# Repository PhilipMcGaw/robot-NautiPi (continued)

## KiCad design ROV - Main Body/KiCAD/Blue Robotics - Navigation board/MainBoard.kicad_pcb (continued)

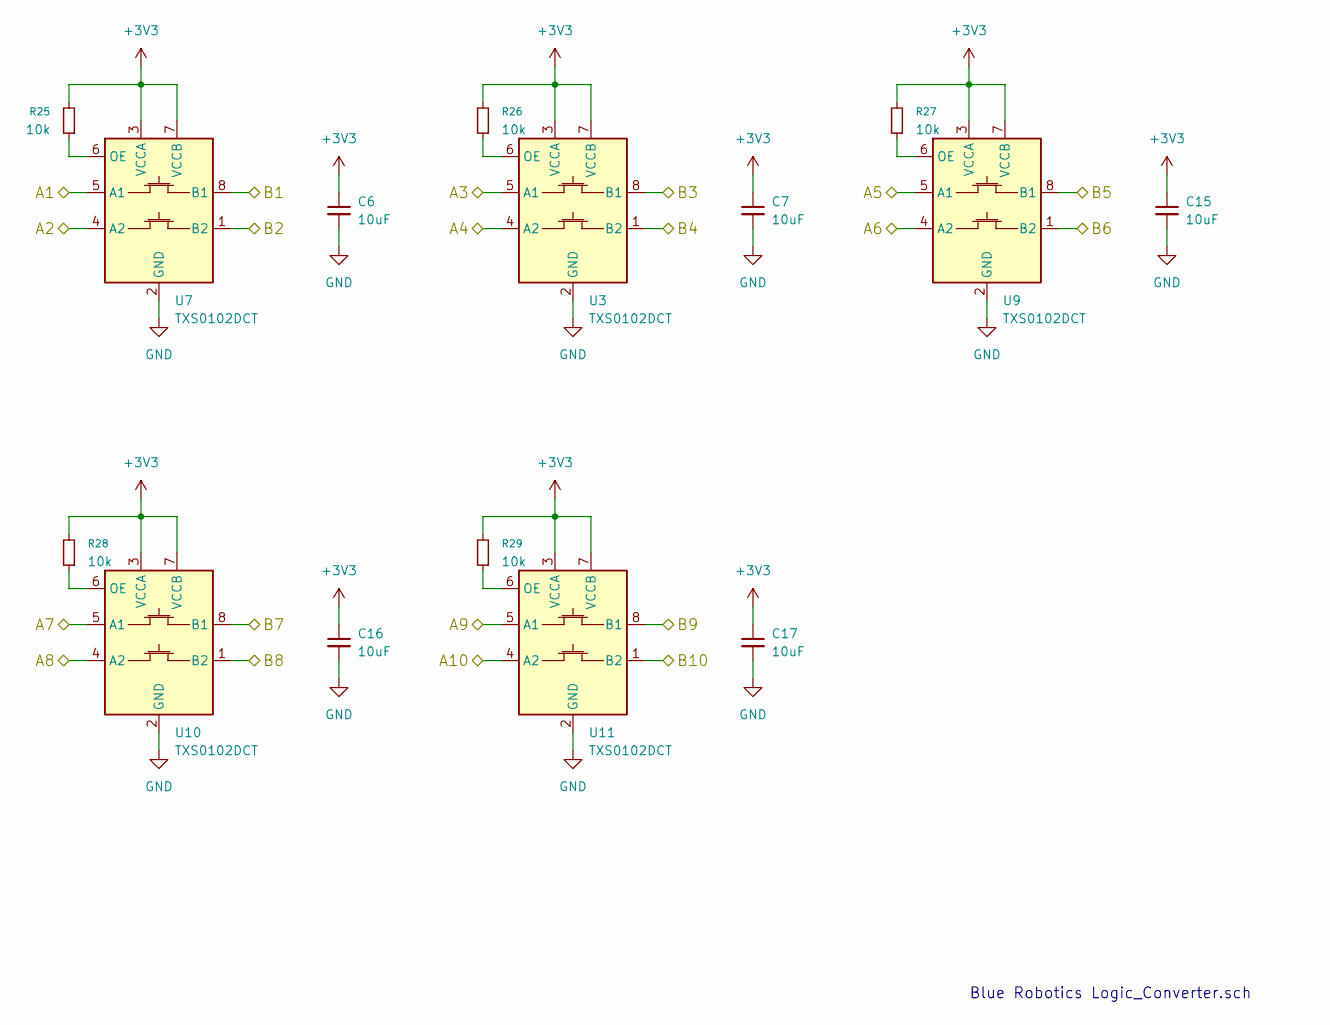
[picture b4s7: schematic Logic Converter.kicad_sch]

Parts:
C6, C7, C15, C16, C17: 10uF; C_0805_2012Metric_Pad1.18x1.45mm_HandSolder
R25, R26, R27, R28, R29: 10k; R_0805_2012Metric_Pad1.20x1.40mm_HandSolder
U3, U7, U9, U10, U11: TXS0102DCT; SSOP-8_2.95x2.8mm_P0.65mm; Farnell 3120980

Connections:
+3V3: C6.1, C7.1, C15.1, C16.1, C17.1, R25.2, R26.2, R27.2, R28.2, R29.2, U3.3 (VCCA), U3.7 (VCCB), U7.3 (VCCA), U7.7 (VCCB), U9.3 (VCCA), U9.7 (VCCB), U10.3 (VCCA), U10.7 (VCCB), U11.3 (VCCA), U11.7 (VCCB); also elsewhere on the board
/RX1: U7.8 (B1); also elsewhere on the board
/RX1_RPI: U7.5 (A1); also elsewhere on the board
/RX3: U3.8 (B1); also elsewhere on the board
/RX3_RPI: U3.5 (A1); also elsewhere on the board
/RX4: U9.1 (B2); also elsewhere on the board
/RX4_RPI: U9.4 (A2); also elsewhere on the board
/RX5: U10.8 (B1); also elsewhere on the board
/RX5_RPI: U10.5 (A1); also elsewhere on the board
/SCL6: U11.8 (B1); also elsewhere on the board
/SCL6_RPI: U11.5 (A1); also elsewhere on the board
/SDA6: U11.1 (B2); also elsewhere on the board
/SDA6_RPI: U11.4 (A2); also elsewhere on the board
/TX1: U7.1 (B2); also elsewhere on the board
/TX1_RPI: U7.4 (A2); also elsewhere on the board
/TX3: U3.1 (B2); also elsewhere on the board
/TX3_RPI: U3.4 (A2); also elsewhere on the board
/TX4: U9.8 (B1); also elsewhere on the board
/TX4_RPI: U9.5 (A1); also elsewhere on the board
/TX5: U10.1 (B2); also elsewhere on the board
/TX5_RPI: U10.4 (A2); also elsewhere on the board
GND: C6.2, C7.2, C15.2, C16.2, C17.2, U3.2 (GND), U7.2 (GND), U9.2 (GND), U10.2 (GND), U11.2 (GND); also elsewhere on the board
unnamed: R26.1, U3.6 (OE)
unnamed: R25.1, U7.6 (OE)
unnamed: R27.1, U9.6 (OE)
unnamed: R28.1, U10.6 (OE)
unnamed: R29.1, U11.6 (OE)

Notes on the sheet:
Blue Robotics Logic_Converter.sch

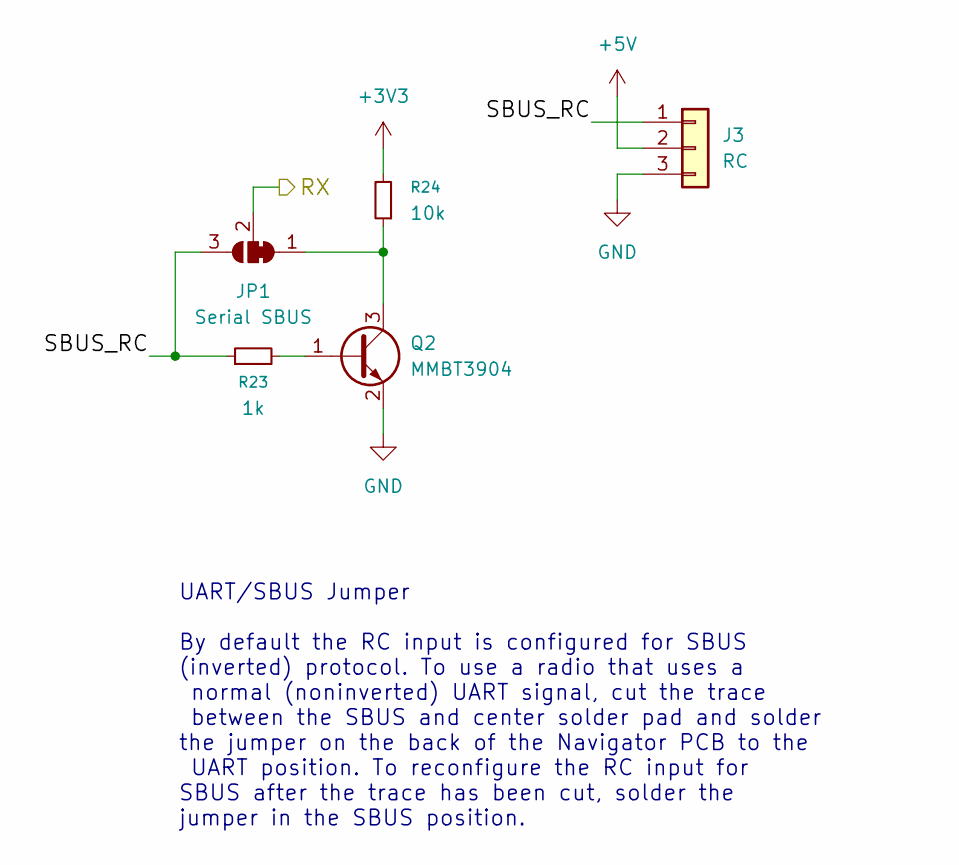
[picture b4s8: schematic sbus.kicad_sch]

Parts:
J3: RC; PinHeader_1x03_P2.54mm_Vertical
JP1: Serial SBUS; SolderJumper-3_P1.3mm_Bridged12_RoundedPad1.0x1.5mm
Q2: MMBT3904; SOT-23
R23: 1k; R_0805_2012Metric_Pad1.20x1.40mm_HandSolder
R24: 10k; R_0805_2012Metric_Pad1.20x1.40mm_HandSolder

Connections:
+3V3: R24.2; also elsewhere on the board
+5V: J3.2; also elsewhere on the board
/RX1: JP1.2 (C); also elsewhere on the board
/SBUS/SBUS_RC: J3.1, JP1.3 (B), R23.1
GND: J3.3, Q2.2 (E); also elsewhere on the board
unnamed: JP1.1 (A), Q2.3 (C), R24.1
unnamed: Q2.1 (B), R23.2

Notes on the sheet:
UART/SBUS Jumper By default the RC input is configured for SBUS (inverted) protocol. To use a radio that uses a normal (noninverted) UART signal, cut the trace between the SBUS and center solder pad and solder the jumper on the back of the Navigator PCB to the UART position. To reconfigure the RC i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

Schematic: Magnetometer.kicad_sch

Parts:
C27: 10uF; C_0805_2012Metric_Pad1.18x1.45mm_HandSolder
C28: 1uF; C_0805_2012Metric_Pad1.18x1.45mm_HandSolder
C29, C30: 100nF; C_0805_2012Metric_Pad1.18x1.45mm_HandSolder

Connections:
+3V3: C27.1, C28.1, C29.1, C30.1; also elsewhere on the board
GND: C27.2, C28.2, C29.2, C30.2; also elsewhere on the board

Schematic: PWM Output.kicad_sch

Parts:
J2: PWM 1-4; JST_GH_BM05B-GHS-TBT_1x05-1MP_P1.25mm_Vertical
J4: PWM 5-8; JST_GH_BM05B-GHS-TBT_1x05-1MP_P1.25mm_Vertical
J11: Servo04; PinHeader_1x03_P2.54mm_Vertical
J12: Servo01; PinHeader_1x03_P2.54mm_Vertical
J13: Servo05; PinHeader_1x03_P2.54mm_Vertical
J14: Servo06; PinHeader_1x03_P2.54mm_Vertical
J15: Servo07; PinHeader_1x03_P2.54mm_Vertical
J16: Servo08; PinHeader_1x03_P2.54mm_Vertical
J21: Servo09; PinHeader_1x03_P2.54mm_Vertical
J25: Servo10; PinHeader_1x03_P2.54mm_Vertical
J26: Servo11; PinHeader_1x03_P2.54mm_Vertical
J27: Servo12; PinHeader_1x03_P2.54mm_Vertical
J28: Servo13; PinHeader_1x03_P2.54mm_Vertical
J29: Servo14; PinHeader_1x03_P2.54mm_Vertical
J30: Servo15; PinHeader_1x03_P2.54mm_Vertical
J31: Servo16; PinHeader_1x03_P2.54mm_Vertical
J32: Servo02; PinHeader_1x03_P2.54mm_Vertical
J41: Servo03; PinHeader_1x03_P2.54mm_Vertical
R44: 10k; R_0805_2012Metric_Pad1.20x1.40mm_HandSolder
RN1, RN2, RN3, RN4: 220; R_Array_Convex_4x1206
U1: PCA9685PW; TSSOP-28_4.4x9.7mm_P0.65mm

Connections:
+3V3: R44.1, U1.28 (VDD); also elsewhere on the board
/PWM Output/PWM01: J2.1, J12.1, RN1.8 (R1.2)
/PWM Output/PWM02: J2.2, J32.1, RN1.7 (R2.2)
/PWM Output/PWM03: J2.3, J41.1, RN1.6 (R3.2)
/PWM Output/PWM04: J2.4, J11.1, RN1.5 (R4.2)
/PWM Output/PWM05: J4.1, J13.1, RN2.8 (R1.2)
/PWM Output/PWM06: J4.2, J14.1, RN2.7 (R2.2)
/PWM Output/PWM07: J4.3, J15.1, RN2.6 (R3.2)
/PWM Output/PWM08: J4.4, J16.1, RN2.5 (R4.2)
/PWM Output/PWM09: J21.1, RN3.8 (R1.2)
/PWM Output/PWM10: J25.1, RN3.7 (R2.2)
/PWM Output/PWM11: J26.1, RN3.6 (R3.2)
/PWM Output/PWM12: J27.1, RN3.5 (R4.2)
/PWM Output/PWM13: J28.1, RN4.8 (R1.2)
/PWM Output/PWM14: J29.1, RN4.7 (R2.2)
/PWM Output/PWM15: J30.1, RN4.6 (R3.2)
/PWM Output/PWM16: J31.1, RN4.5 (R4.2)
/PWM_OE: R44.2, U1.23 (~OE); also elsewhere on the board
/SCL4: U1.26 (SCL); also elsewhere on the board
/SDA4: U1.27 (SDA); also elsewhere on the board
GND: J2.5, J4.5, J11.3, J12.3, J13.3, J14.3, J15.3, J16.3, J21.3, J25.3, J26.3, J27.3, J28.3, J29.3, J30.3, J31.3, J32.3, J41.3, U1.1 (A0), U1.2 (A1), U1.3 (A2), U1.4 (A3), U1.5 (A4), U1.14 (VSS), U1.24 (A5), U1.25 (EXTCLK); also elsewhere on the board
unnamed: RN1.1 (R1.1), U1.6 (LED0)
unnamed: RN1.2 (R2.1), U1.7 (LED1)
unnamed: RN1.3 (R3.1), U1.8 (LED2)
unnamed: RN1.4 (R4.1), U1.9 (LED3)
unnamed: RN2.1 (R1.1), U1.10 (LED4)
unnamed: RN2.2 (R2.1), U1.11 (LED5)
unnamed: RN2.3 (R3.1), U1.12 (LED6)
unnamed: RN2.4 (R4.1), U1.13 (LED7)
unnamed: RN3.1 (R1.1), U1.15 (LED8)
unnamed: RN3.2 (R2.1), U1.16 (LED9)
unnamed: RN3.3 (R3.1), U1.17 (LED10)
unnamed: RN3.4 (R4.1), U1.18 (LED11)
unnamed: RN4.1 (R1.1), U1.19 (LED12)
unnamed: RN4.2 (R2.1), U1.20 (LED13)
unnamed: RN4.3 (R3.1), U1.21 (LED14)
unnamed: RN4.4 (R4.1), U1.22 (LED15)
SERVO_BEC: J11.2, J12.2, J13.2, J14.2, J15.2, J16.2, J21.2, J25.2, J26.2, J27.2, J28.2, J29.2, J30.2, J31.2, J32.2, J41.2; also elsewhere on the board

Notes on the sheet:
This is dervied from the Blue Robotics pwm-output.sch Local X1 has been ommited, and external clock taken to ground. Servo connectors have been broken out onto 1x03 connectors
Mating JST GH Plug and Crimp Pins GHR-05V-S (housing) SSHL-002T-P0.2 (pin)

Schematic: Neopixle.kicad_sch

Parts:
C20: 100nF; C_0805_2012Metric_Pad1.18x1.45mm_HandSolder
D20: WS2812B; LED_WS2812B_PLCC4_5.0x5.0mm_P3.2mm

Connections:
+5V: C20.1, D20.1 (VDD); also elsewhere on the board
/RGB_LED: D20.4 (DIN); also elsewhere on the board
GND: C20.2, D20.3 (VSS); also elsewhere on the board

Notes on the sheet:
This is dervied from the Blue Robotics neopixel.sch Local U13 has been ommited, and neopixle has been changed from SK6812 to a WS2812B.

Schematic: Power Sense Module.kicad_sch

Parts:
C18: 0.1uF; C_0805_2012Metric_Pad1.18x1.45mm_HandSolder
C19: 1uF; C_0805_2012Metric_Pad1.18x1.45mm_HandSolder
R3: 4.7k; R_0805_2012Metric_Pad1.20x1.40mm_HandSolder
R12: 47.5k; R_0805_2012Metric_Pad1.20x1.40mm_HandSolder
R13: 4.75k; R_0805_2012Metric_Pad1.20x1.40mm_HandSolder
U6: ACS781xLRTR-100U; Allegro_PSOF-7_4.8x6.4mm_P1.60mm

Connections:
+3V3: C18.1, U6.1 (VCC); also elsewhere on the board
+14V_MEASURED: R12.2, U6.6 (IP-); also elsewhere on the board
+14V_SUPPLY: U6.5 (IP+); also elsewhere on the board
/Analog Input/ADC2: C19.1, R3.2; also elsewhere on the board
/Analog Input/ADC3: R12.1, R13.2; also elsewhere on the board
GND: C18.2, C19.2, R13.1, U6.2 (GND); also elsewhere on the board
unnamed: R3.1, U6.3 (VOUT)

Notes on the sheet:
This is dervied from the Blue Robotics PSM-ELEC-PCB-R2 Power Sende Moule PCB Local regulator has been ommited, as has Power LED and 6 pin header.
35 Vout = 3.182 V_Sense 20 Vout = 1.818 V_Sense 14 Vout = 1.273 V_Sense

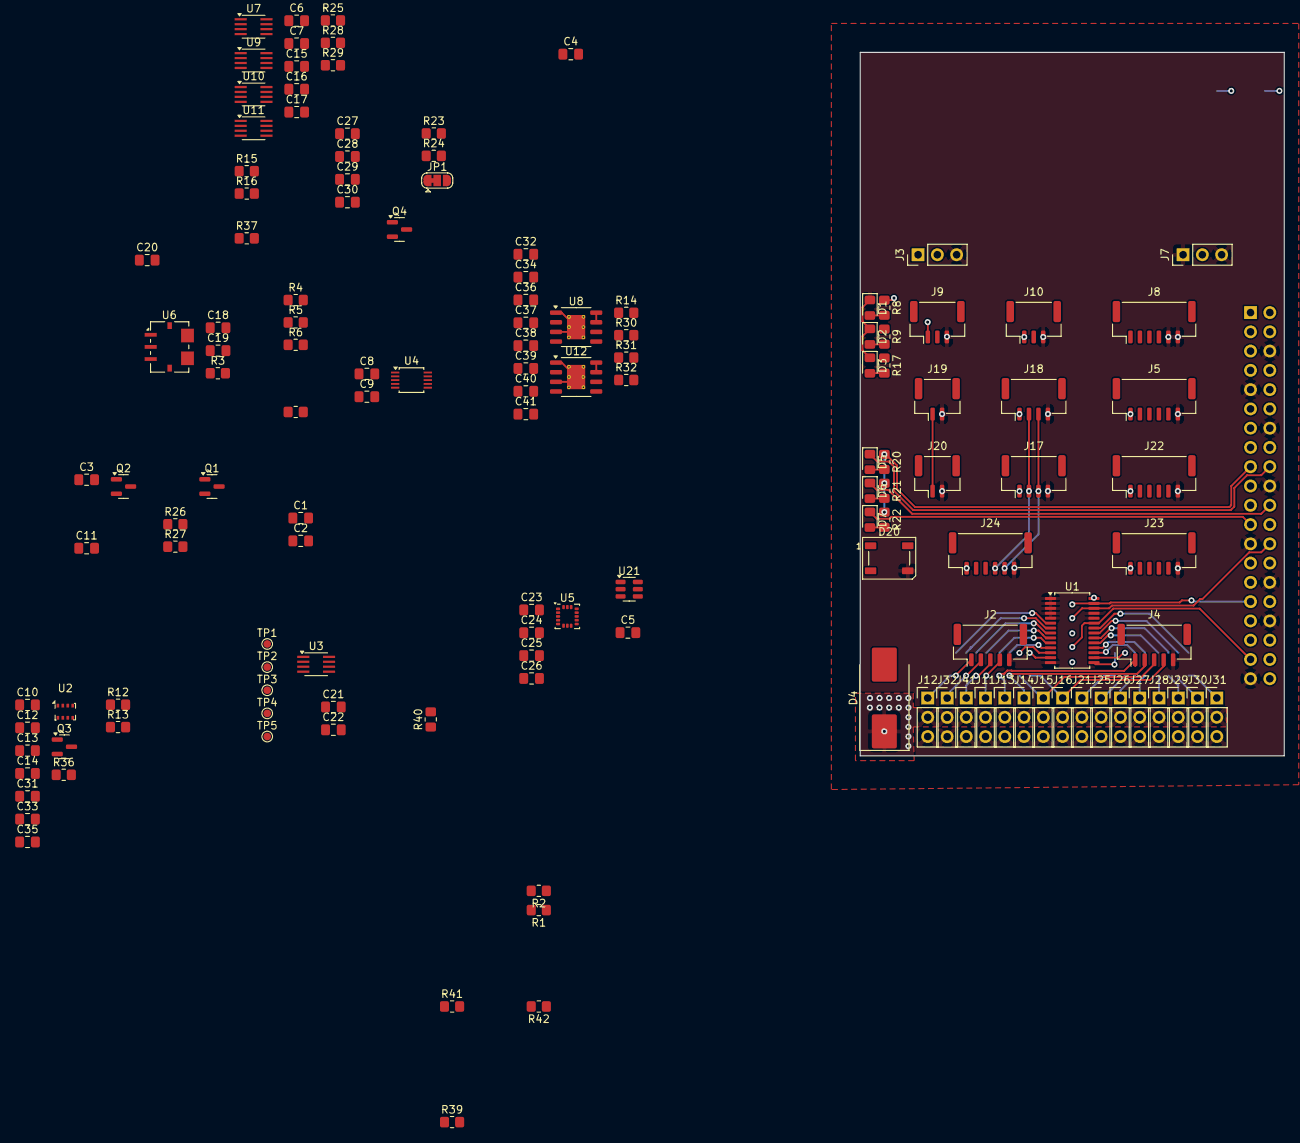
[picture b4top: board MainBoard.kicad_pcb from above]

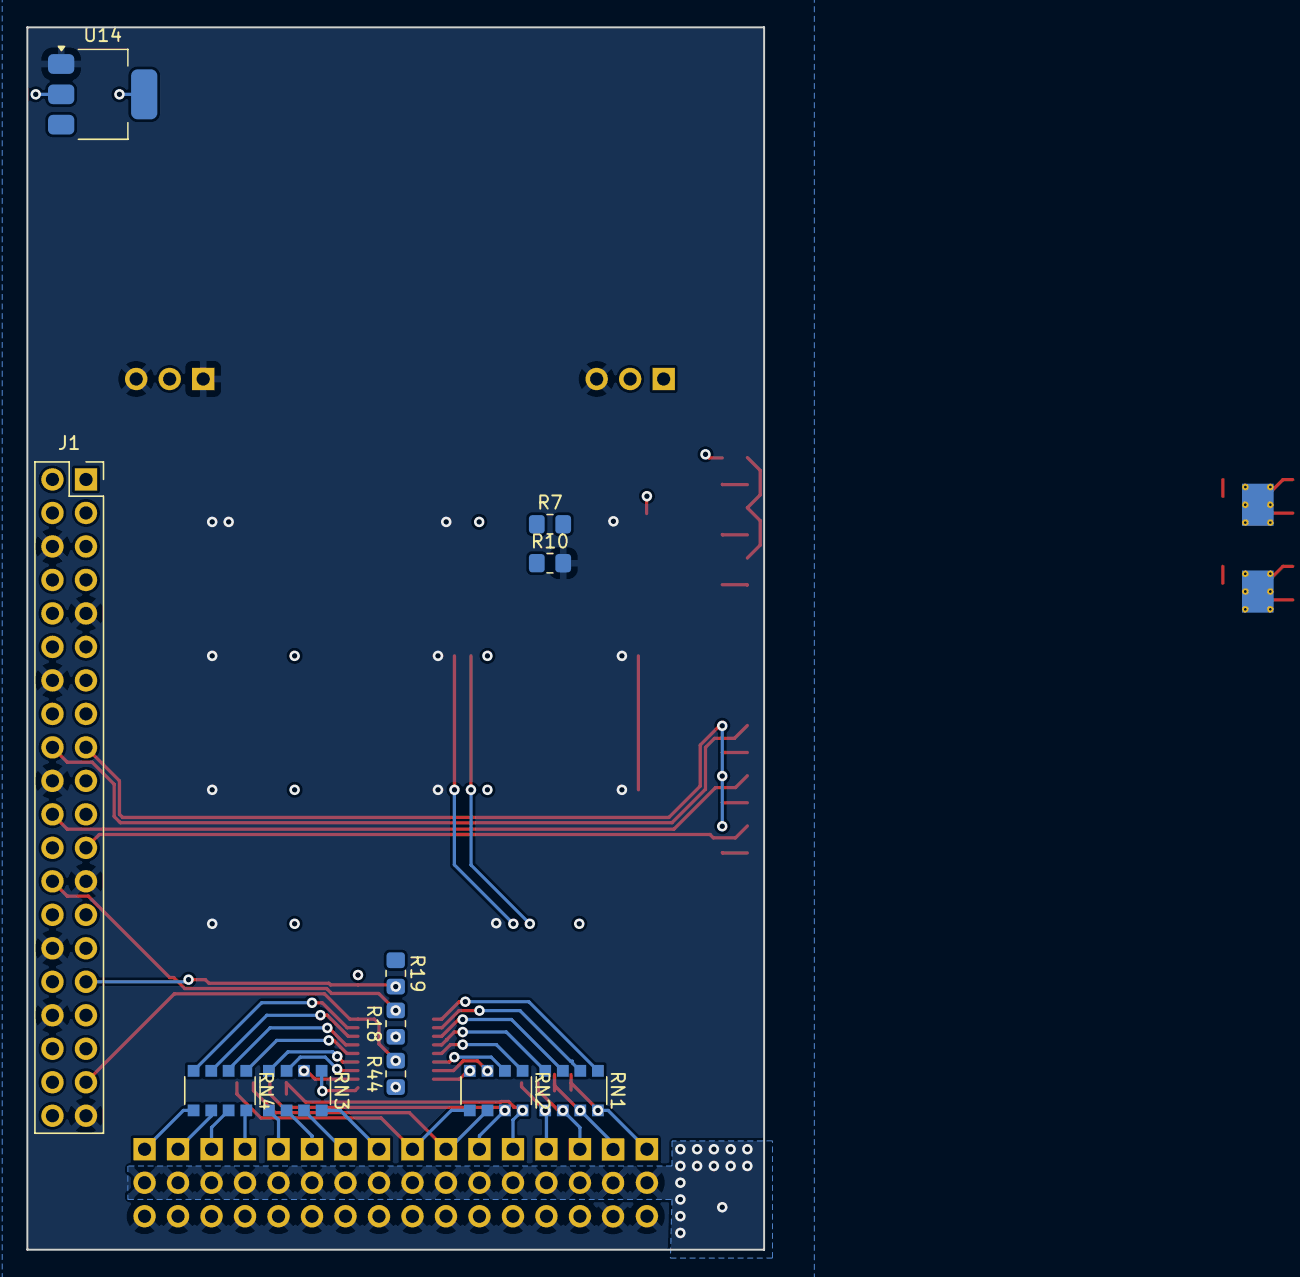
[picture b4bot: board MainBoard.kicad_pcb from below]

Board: 4 copper layers, 55.9 x 92.7 mm, 148 parts (11 on the bottom side), 109 nets.

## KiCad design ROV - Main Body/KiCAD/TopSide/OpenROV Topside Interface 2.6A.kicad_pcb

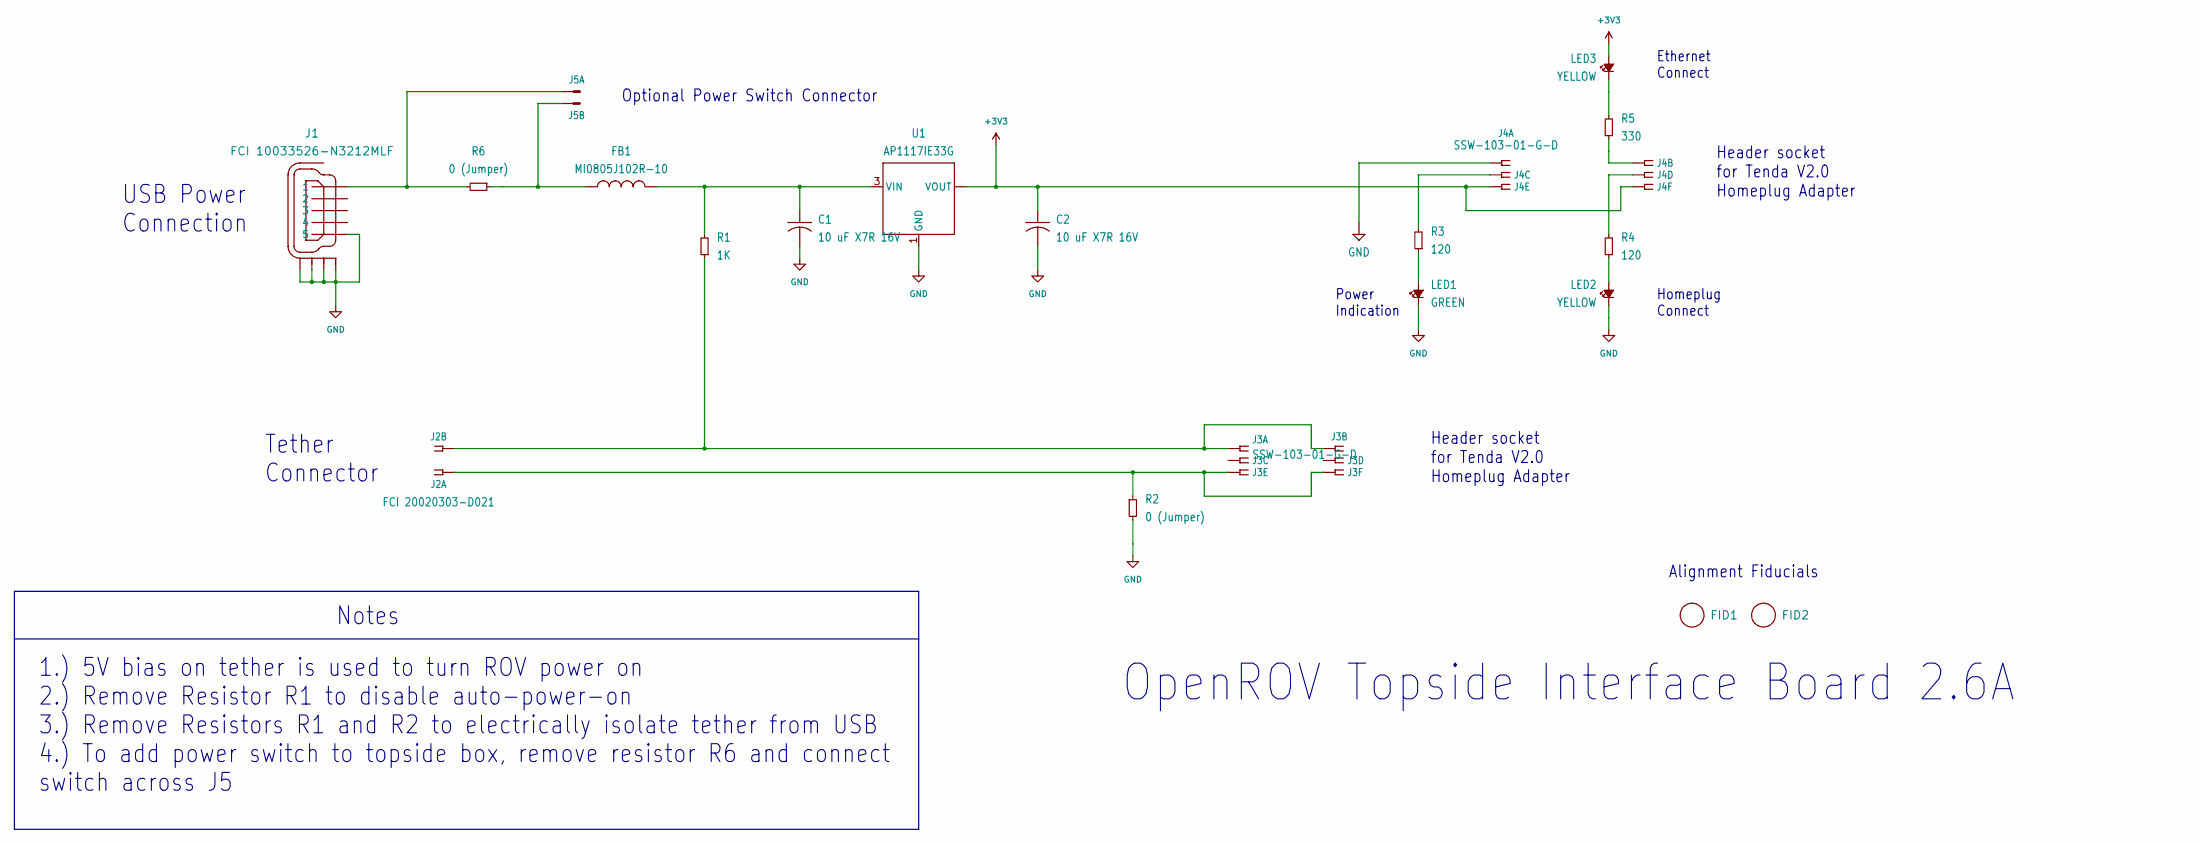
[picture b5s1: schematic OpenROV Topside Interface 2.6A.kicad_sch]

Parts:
C1, C2: 10 uF X7R 16V; R1206
FB1: MI0805J102R-10; R0805
FID1, FID2: FIDUCIAL_1
J1: FCI 10033526-N3212MLF; USB_MINI-B_SM
J2: FCI 20020303-D021; FCI_09-381_2PL
J3, J4: SSW-103-01-G-D; SSW-103-02-S-D
J5: HDR_1X2X0.100-ALT_SILK; 22-23-2021_ALT_SILK
LED1: GREEN; LED_0805_2012Metric_Pad1.15x1.40mm_HandSolder
LED2, LED3: YELLOW; LED_0805_2012Metric_Pad1.15x1.40mm_HandSolder
R1: 1K; R0805
R2, R6: 0 (Jumper); R_0805_2012Metric_Pad1.20x1.40mm_HandSolder
R3, R4: 120; R0805
R5: 330; R0805
U1: AP1117IE33G; SOT223

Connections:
+3V3: C2.1, J4.5 (1), J4.6 (1), LED3.2 (A), U1.2 (VOUT), U1.4 (VOUT)
GND: C1.2, C2.2, J1.5, J1.M1 (S1), J1.M2 (S2), J1.M3 (S3), J1.M4 (S4), J4.1, LED1.1 (K), LED2.1 (K), R2.2, U1.1 (GND)
unnamed: J2.2A (1), J2.2B (1), J3.1, J3.2 (1), R1.1
unnamed: J2.1A (1), J2.1B (1), J3.5 (1), J3.6 (1), R2.1
unnamed: J4.2 (1), R5.1
unnamed: J4.3 (1), R3.2
unnamed: J4.4 (1), R4.2
unnamed: J1.1, J5.1 (S), R6.2
unnamed: FB1.1, J5.2 (S), R6.1
unnamed: LED1.2 (A), R3.1
unnamed: LED2.2 (A), R4.1
unnamed: LED3.1 (K), R5.2
unnamed: C1.1, FB1.2, R1.2, U1.3 (VIN)

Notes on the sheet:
1.) 5V bias on tether is used to turn ROV power on 2.) Remove Resistor R1 to disable auto-power-on 3.) Remove Resistors R1 and R2 to electrically isolate tether from USB 4.) To add power switch to topside box, remove resistor R6 and connect switch across J5
Alignment Fiducials
Homeplug Connect
USB Power Connection
Power Indication
Optional Power Switch Connector
Header socket for Tenda V2.0 Homeplug Adapter
Notes
OpenROV Topside Interface Board 2.6A
Tether Connector
Ethernet Connect

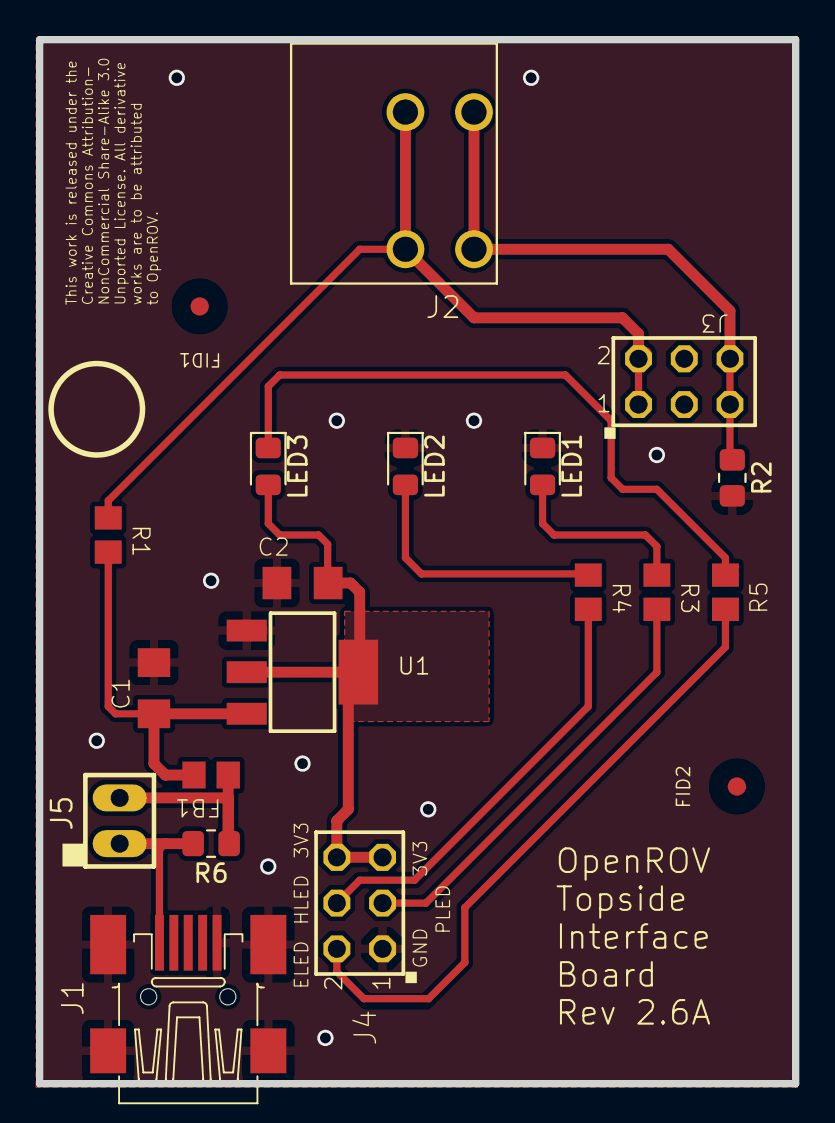
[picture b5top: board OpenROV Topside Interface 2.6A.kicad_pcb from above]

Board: 4 copper layers, 42.0 x 58.0 mm, 20 parts (0 on the bottom side), 13 nets.

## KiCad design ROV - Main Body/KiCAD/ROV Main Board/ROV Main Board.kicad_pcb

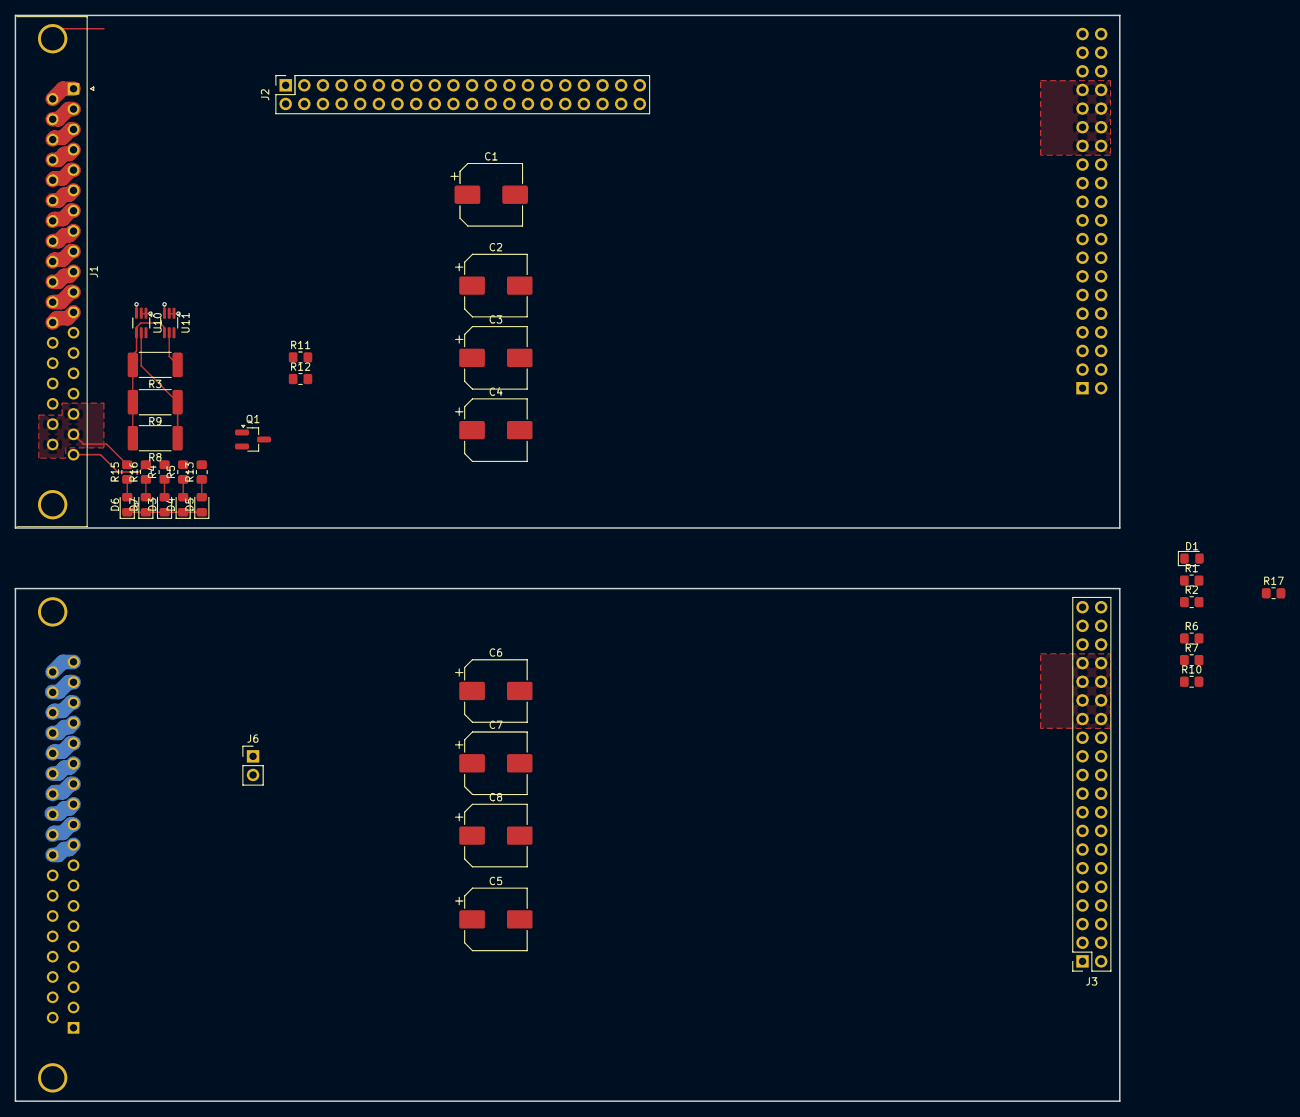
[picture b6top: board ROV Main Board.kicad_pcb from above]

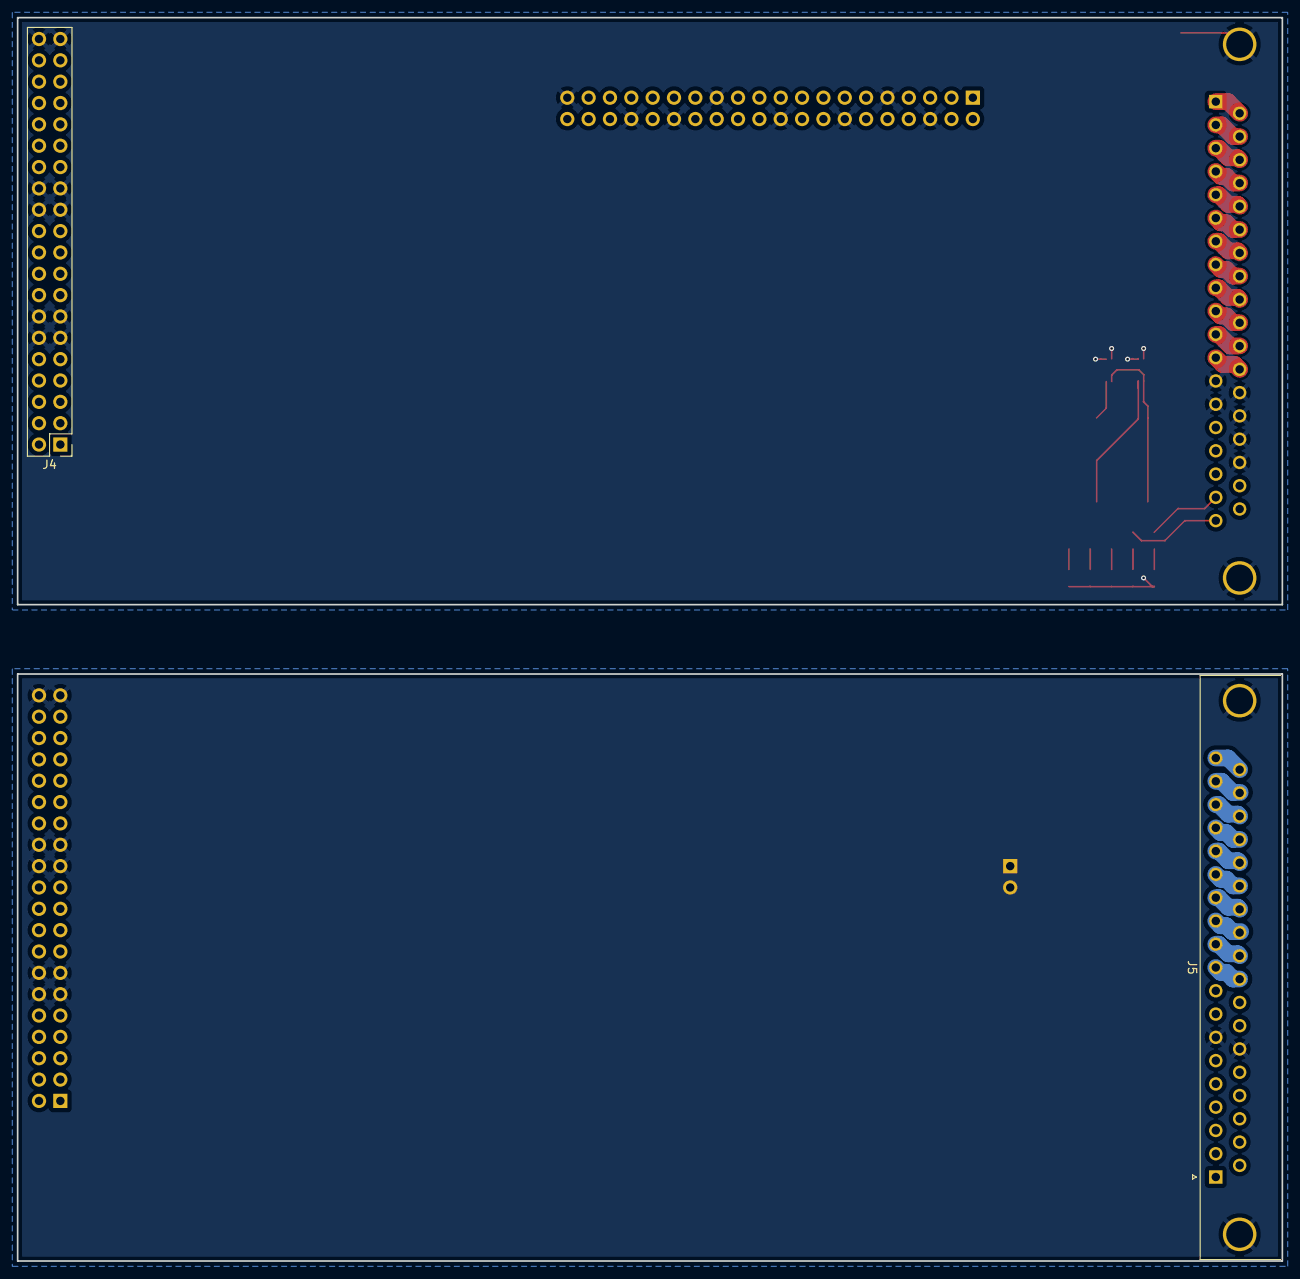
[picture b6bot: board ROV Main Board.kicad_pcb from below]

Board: 2 copper layers, 150.5 x 148.0 mm, 39 parts (2 on the bottom side), 44 nets.

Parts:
C1, C2, C3, C4, C5, C6, C7, C8: 220uF/25V; CP_Elec_8x10
D1: LED; LED_0805_2012Metric_Pad1.15x1.40mm_HandSolder
D3: +VE; LED_0805_2012Metric_Pad1.15x1.40mm_HandSolder
D4: 5V; LED_0805_2012Metric_Pad1.15x1.40mm_HandSolder
D5: Leak; LED_0805_2012Metric_Pad1.15x1.40mm_HandSolder
D6: Harness V+; LED_0805_2012Metric_Pad1.15x1.40mm_HandSolder
D7: Harness 5V; LED_0805_2012Metric_Pad1.15x1.40mm_HandSolder
J1: Top; DSUB-37_Pins_Horizontal_P2.77x2.84mm_EdgePinOffset4.94mm_Ho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
J2: Raspberry_Pi_4; PinSocket_2x20_P2.54mm_Vertical
J3: Bottom; PinSocket_2x20_P2.54mm_Vertical
J4: Top; PinHeader_2x20_P2.54mm_Vertical
J5: Bottom; DSUB-37_Pins_Horizontal_P2.77x2.84mm_EdgePinOffset4.94mm_Ho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
J6: Conn_01x02_Socket; PinHeader_1x02_P2.54mm_Vertical
Q1: MMBT3906; SOT-23_Handsoldering
R1, R2: 330; R_0805_2012Metric_Pad1.20x1.40mm_HandSolder
R3, R8, R9: 0.003 %1; R_2512_6332Metric_Pad1.40x3.35mm_HandSolder
R4: 0; R_0805_2012Metric_Pad1.20x1.40mm_HandSolder
R5, R16: 560; R_0805_2012Metric_Pad1.20x1.40mm_HandSolder
R6: 30.1k 1%; R_0805_2012Metric_Pad1.20x1.40mm_HandSolder
R7: 10k %1; R_0805_2012Metric_Pad1.20x1.40mm_HandSolder
R10, R17: 3.3k; R_0805_2012Metric_Pad1.20x1.40mm_HandSolder
R11: 20k; R_0805_2012Metric_Pad1.20x1.40mm_HandSolder
R12: 1k; R_0805_2012Metric_Pad1.20x1.40mm_HandSolder
R13: 120; R_0805_2012Metric_Pad1.20x1.40mm_HandSolder
R15: 1k8; R_0805_2012Metric_Pad1.20x1.40mm_HandSolder
U10, U11: INA199A2; SOT-363_SC-70-6_Handsoldering

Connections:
5V: J2.2 (5V), J2.4 (5V), R5.2
+5V: J3.4, J3.8, J4.4, J4.8, Q1.3 (C), R11.2, U10.3 (V+), U11.3 (V+)
+24V Int: J3.3, J3.7, J4.3, J4.7, R3.1, R6.1, U11.5 (IN-)
/Bottom PCB/Bottom PCB Harness Interface/MOTOR_5A: J5.8, J5.26
/Bottom PCB/Bottom PCB Harness Interface/MOTOR_5B: J5.9, J5.27
/Bottom PCB/Bottom PCB Harness Interface/MOTOR_5C: J5.10, J5.28
/Bottom PCB/Bottom PCB Harness Interface/MOTOR_6A: J5.11, J5.29
/Bottom PCB/Bottom PCB Harness Interface/MOTOR_6B: J5.12, J5.30
/Bottom PCB/Bottom PCB Harness Interface/MOTOR_6C: J5.13, J5.31
/Bottom PCB/Bottom PCB Harness Interface/MOTOR_7A: J5.14, J5.32
/Bottom PCB/Bottom PCB Harness Interface/MOTOR_7B: J5.15, J5.33
/Bottom PCB/Bottom PCB Harness Interface/MOTOR_7C: J5.16, J5.34
/Bottom PCB/Bottom PCB Harness Interface/MOTOR_8A: J5.17, J5.35
/Bottom PCB/Bottom PCB Harness Interface/MOTOR_8B: J5.18, J5.36
/Bottom PCB/Bottom PCB Harness Interface/MOTOR_8C: J5.19, J5.37
/Top PCB/Brushless DC Controllers/MOTOR_1A: J1.12, J1.31
/Top PCB/Brushless DC Controllers/MOTOR_1B: J1.11, J1.30
/Top PCB/Brushless DC Controllers/MOTOR_1C: J1.10, J1.29
/Top PCB/Brushless DC Controllers/MOTOR_2A: J1.9, J1.28
/Top PCB/Brushless DC Controllers/MOTOR_2B: J1.8, J1.27
/Top PCB/Brushless DC Controllers/MOTOR_2C: J1.7, J1.26
/Top PCB/Brushless DC Controllers/MOTOR_3A: J1.6, J1.25
/Top PCB/Brushless DC Controllers/MOTOR_3B: J1.5, J1.24
/Top PCB/Brushless DC Controllers/MOTOR_3C: J1.4, J1.23
/Top PCB/Brushless DC Controllers/MOTOR_4A: J1.3, J1.22
/Top PCB/Brushless DC Controllers/MOTOR_4B: J1.2, J1.21
/Top PCB/Brushless DC Controllers/MOTOR_4C: J1.1, J1.20
/Top PCB/Leak Detection/Leak_Detect_Signal: Q1.2 (E), R13.2
/Top PCB/Power Managment/ADC_V: R6.2, R7.1
GND: C1.2, C2.2, C3.2, C4.2, C5.2, C6.2, C7.2, C8.2, D1.1 (K), D3.1 (K), D4.1 (K), D5.1 (K), D6.1 (K), D7.1 (K), J1.0 (PAD), J1.13, J1.14, J1.32, J1.33, J1.34, J1.35, J2.6 (GND), J2.9 (GND), J2.14 (GND), J2.20 (GND), J2.25 (GND), J2.30 (GND), J2.34 (GND), J2.39 (GND), J3.11, J3.12, J3.13, J3.14, J3.23, J3.24, J3.25, J3.26, J3.39, J3.40, J4.11, J4.12, J4.13, J4.14, J4.23, J4.24, J4.25, J4.26, J4.39, J4.40, J5.0 (PAD), J5.7, J5.25, R7.2, U10.1 (REF), U10.2 (GND), U11.1 (REF), U11.2 (GND)
Harness 5V IN: J1.19, R16.2
Harness 24V IN: J1.17, J1.18, J1.36, J1.37, R15.2
unnamed: D1.2 (A), R1.2
unnamed: D3.2 (A), R4.1
unnamed: D4.2 (A), R5.1
unnamed: D5.2 (A), R13.1
unnamed: D6.2 (A), R15.1
unnamed: D7.2 (A), R16.1
unnamed: Q1.1 (B), R11.1, R12.1
unnamed: R10.2, U10.6 (OUT)
unnamed: R17.2, U11.6 (OUT)
VIn: R3.2, R8.2, R9.2, U10.4 (IN+), U11.4 (IN+)
V_MOTOR: C1.1, C2.1, C3.1, C4.1, C5.1, C6.1, C7.1, C8.1, J3.27, J3.28, J3.29, J3.30, J3.31, J3.32, J3.33, J3.34, J4.27, J4.28, J4.29, J4.30, J4.31, J4.32, J4.33, J4.34
V_Motors: R8.1, R9.1, U10.5 (IN-)
